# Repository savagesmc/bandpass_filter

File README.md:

# KiCad design of a bandpass filter circuit board

This is an open source schemaatic and board layout for a 9th order chebyshev
filter. The filter was designed on the awesome [filter design tool website.](https://markimicrowave.com/technical-resources/tools/lc-filter-design-tool)

The schematic in this project is for a filter for the UHF band from 240 MHz to 1.2 GHz.

In the [models folder](./models) are a number of different filters that all have the same
shunt first topology, but pass different bands.

The boards that were printed can just be populated with the appropriate L's and C's to put
it into the desired band. The SPICE models included in the [models folder](./models) run 1000
different runs with all of the components varying within the 5% tolerance specified to form a
family of curves that form an envelope of the filter response.

There is an [HF bandpass filter design](./models/hf_filter_9th.spice) from 2.5 MHz to 30 MHz:

There is a [VHF bandpass filter design](./models/vhf_filter_9th.spice) from 30 MHz to 240 MHz:

There is the [UHF bandpass filter design](./models/uhf_filter_9th.spice) that is in the schematic (240 to 1100 MHz):

And there is an [L-Band bandpass filter design](./models/lband_bpf_3rd.spice) from 1000 to 1900 MHz:

I ordered 5 of these boards from [JLCPCB](https://jlcpcb.com). It was a very simple
process. I simply took the contents of the [gerbers folder](./gerbers), zipped
them up and uploaded the zipfile, and for $40 USD (including shipping), and about
2 weeks, I have a set of boards.

Once I have built one of these boards and tested it, I will post the results up here. I am
interested to see how the board parasitics will affect the frequency response of these
boards. I am expecting that the UHF and L-Band circuits will see some noticable deviations from
the spice model filter response. However, the FR4 PCB is supposed to be good for designs all the
way out to 6 GHz, so maybe there won't need to be any adjustments.

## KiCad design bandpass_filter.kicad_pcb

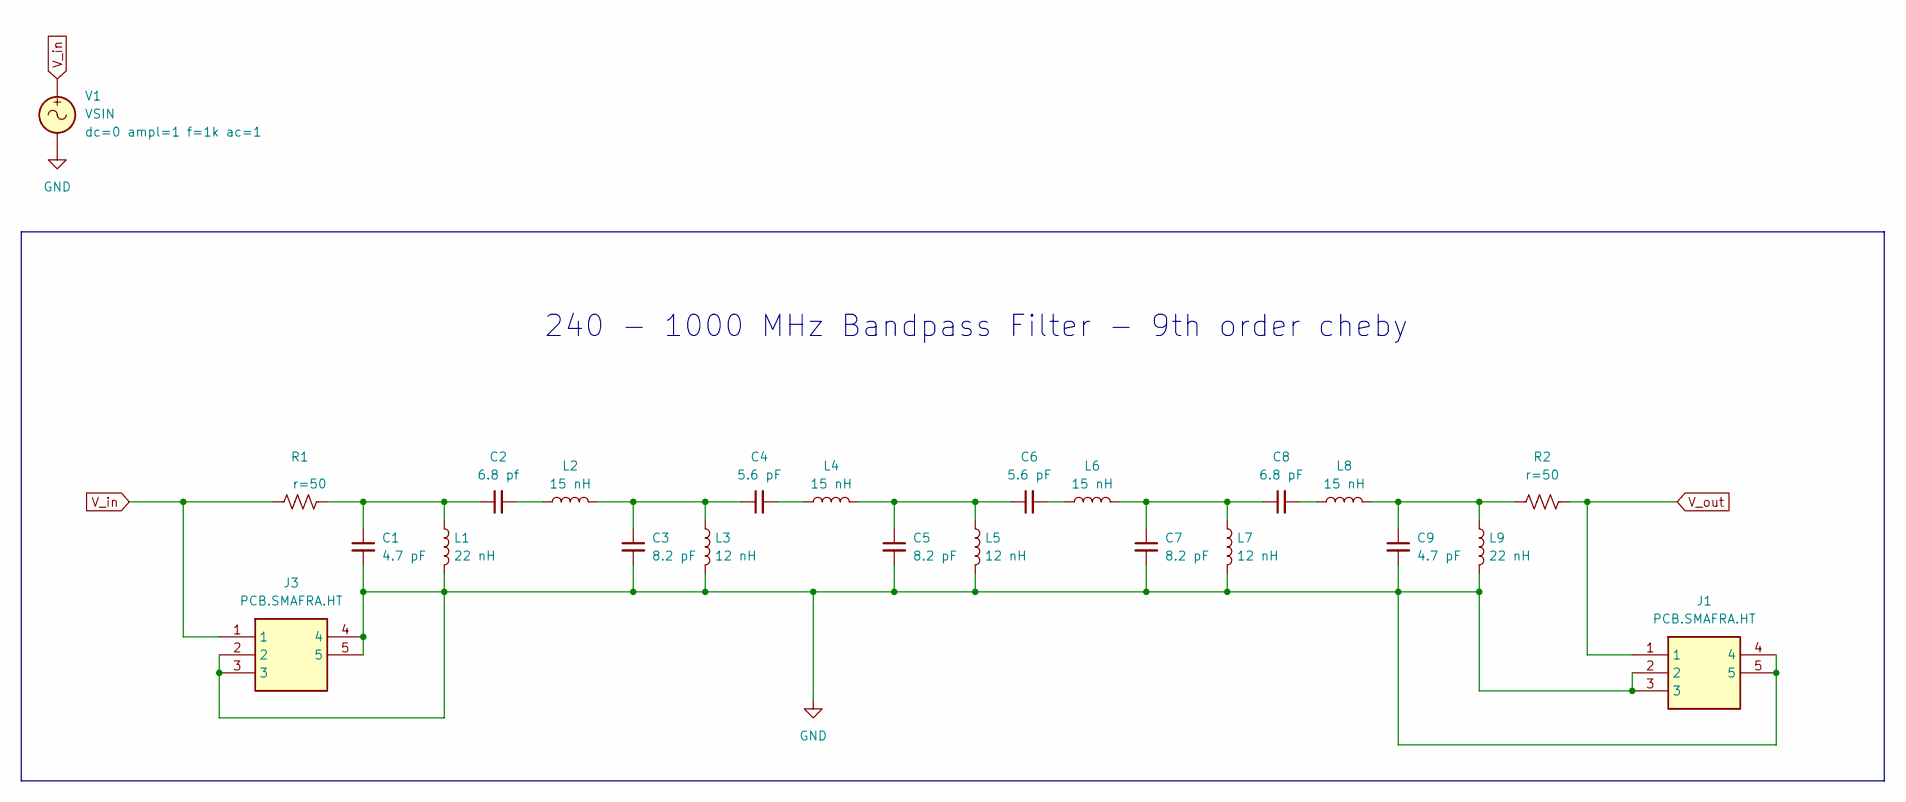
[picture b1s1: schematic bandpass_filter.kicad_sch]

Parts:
C1, C9: 4.7 pF; C_1206_3216Metric
C2: 6.8 pf; C_1206_3216Metric
C3, C5, C7: 8.2 pF; C_1206_3216Metric
C4, C6: 5.6 pF; C_1206_3216Metric
C8: 6.8 pF; C_1206_3216Metric
J1, J3: PCB.SMAFRA.HT; PCBSMAFRAHT; Mouser Part Number 960-PCB.SMAFRA.HT
L1, L9: 22 nH; L_1206_3216Metric
L2, L4, L6, L8: 15 nH; L_1206_3216Metric
L3, L5, L7: 12 nH; L_1206_3216Metric
R1, R2: r=50; R_1206_3216Metric
V1: VSIN

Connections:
GND: C1.2, C3.2, C5.2, C7.2, C9.2, J1.2, J1.3, J1.4, J1.5, J3.2, J3.3, J3.4, J3.5, L1.2, L3.2, L5.2, L7.2, L9.2, V1.2
unnamed: C1.1, C2.1, L1.1, R1.2
unnamed: C2.2, L2.1
unnamed: C3.1, C4.1, L2.2, L3.1
unnamed: C4.2, L4.1
unnamed: C5.1, C6.1, L4.2, L5.1
unnamed: C6.2, L6.1
unnamed: C7.1, C8.1, L6.2, L7.1
unnamed: C8.2, L8.1
unnamed: C9.1, L8.2, L9.1, R2.1
V_in: J3.1, R1.1, V1.1
V_out: J1.1, R2.2

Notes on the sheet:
240 - 1000 MHz Bandpass Filter - 9th order cheby

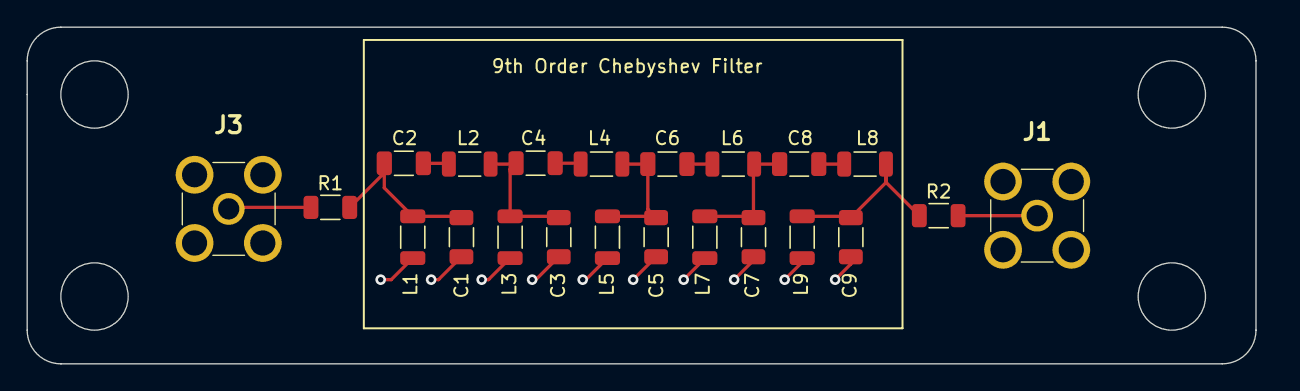
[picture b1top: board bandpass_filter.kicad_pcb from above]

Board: 2 copper layers, 94.0 x 25.4 mm, 22 parts (0 on the bottom side), 12 nets.

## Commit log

2023-10-04 Commit circuit design.
2023-10-04 Add spice model.
2023-10-10 Work on spice model.
2023-10-15 Update README. Add spice models.
